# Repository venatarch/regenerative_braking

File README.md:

# Regenerative Braking Energy Recovery Circuit

## Objective

Recover braking energy from a BLDC motor using bidirectional MOSFET switching.

## Hardware

- STM32
- MOSFET Driver
- Current Sensor
- Voltage Sensor

## Software

- KiCad
- MATLAB
- STM32CubeIDE

## Status

- [x] Literature Review
- [ ] Schematic
- [ ] PCB
- [ ] Firmware
- [ ] Testing

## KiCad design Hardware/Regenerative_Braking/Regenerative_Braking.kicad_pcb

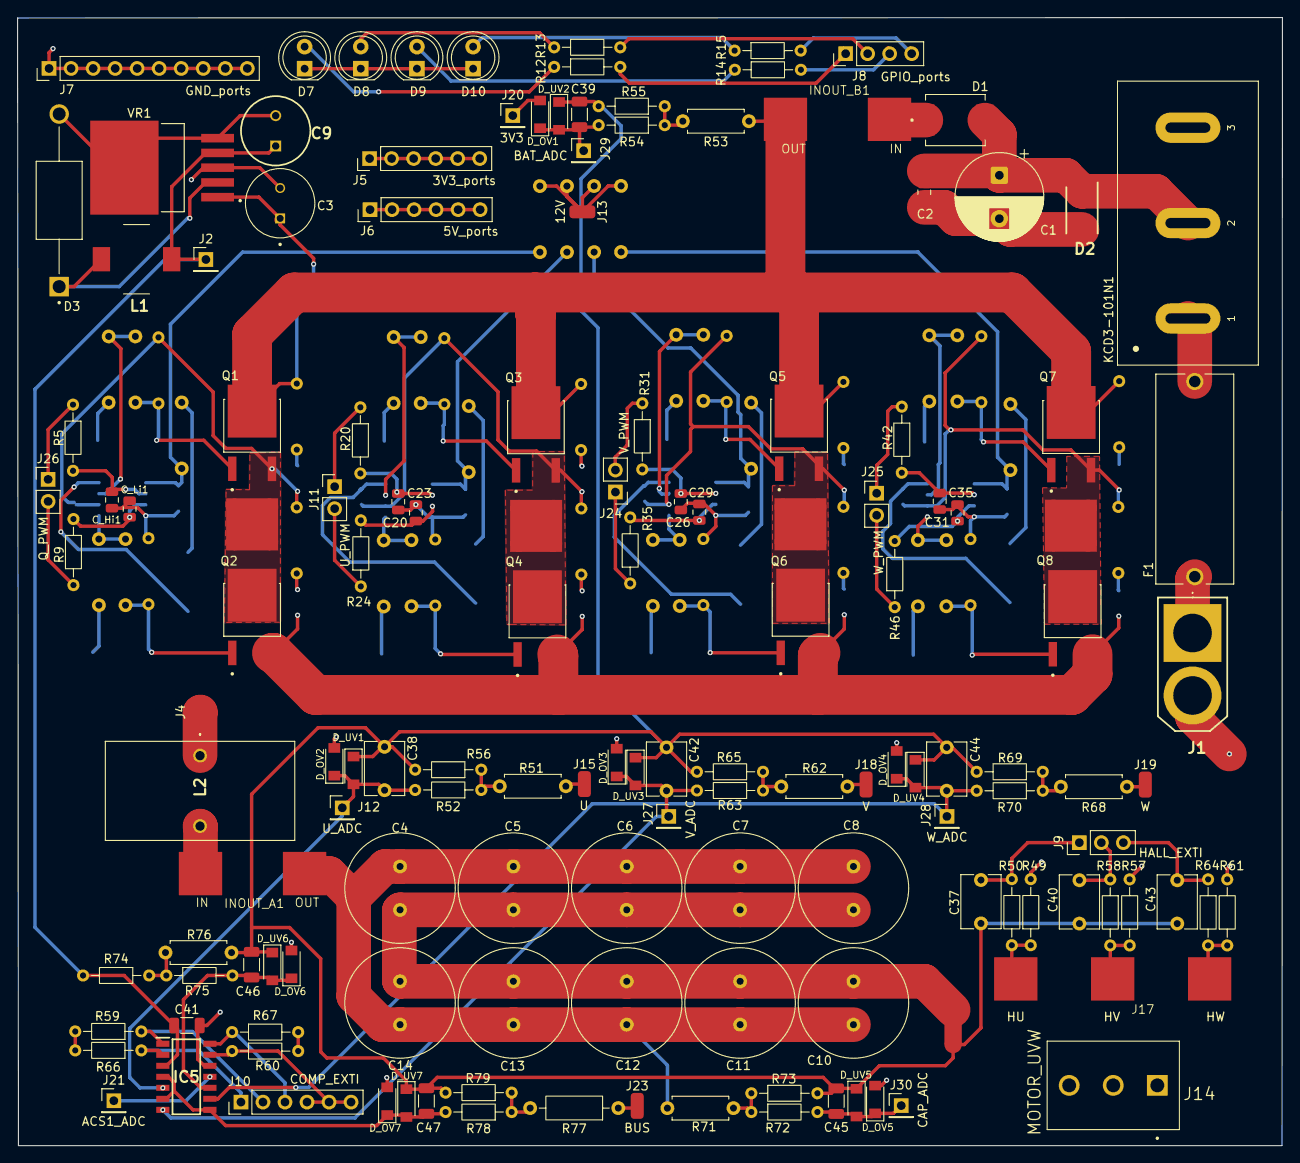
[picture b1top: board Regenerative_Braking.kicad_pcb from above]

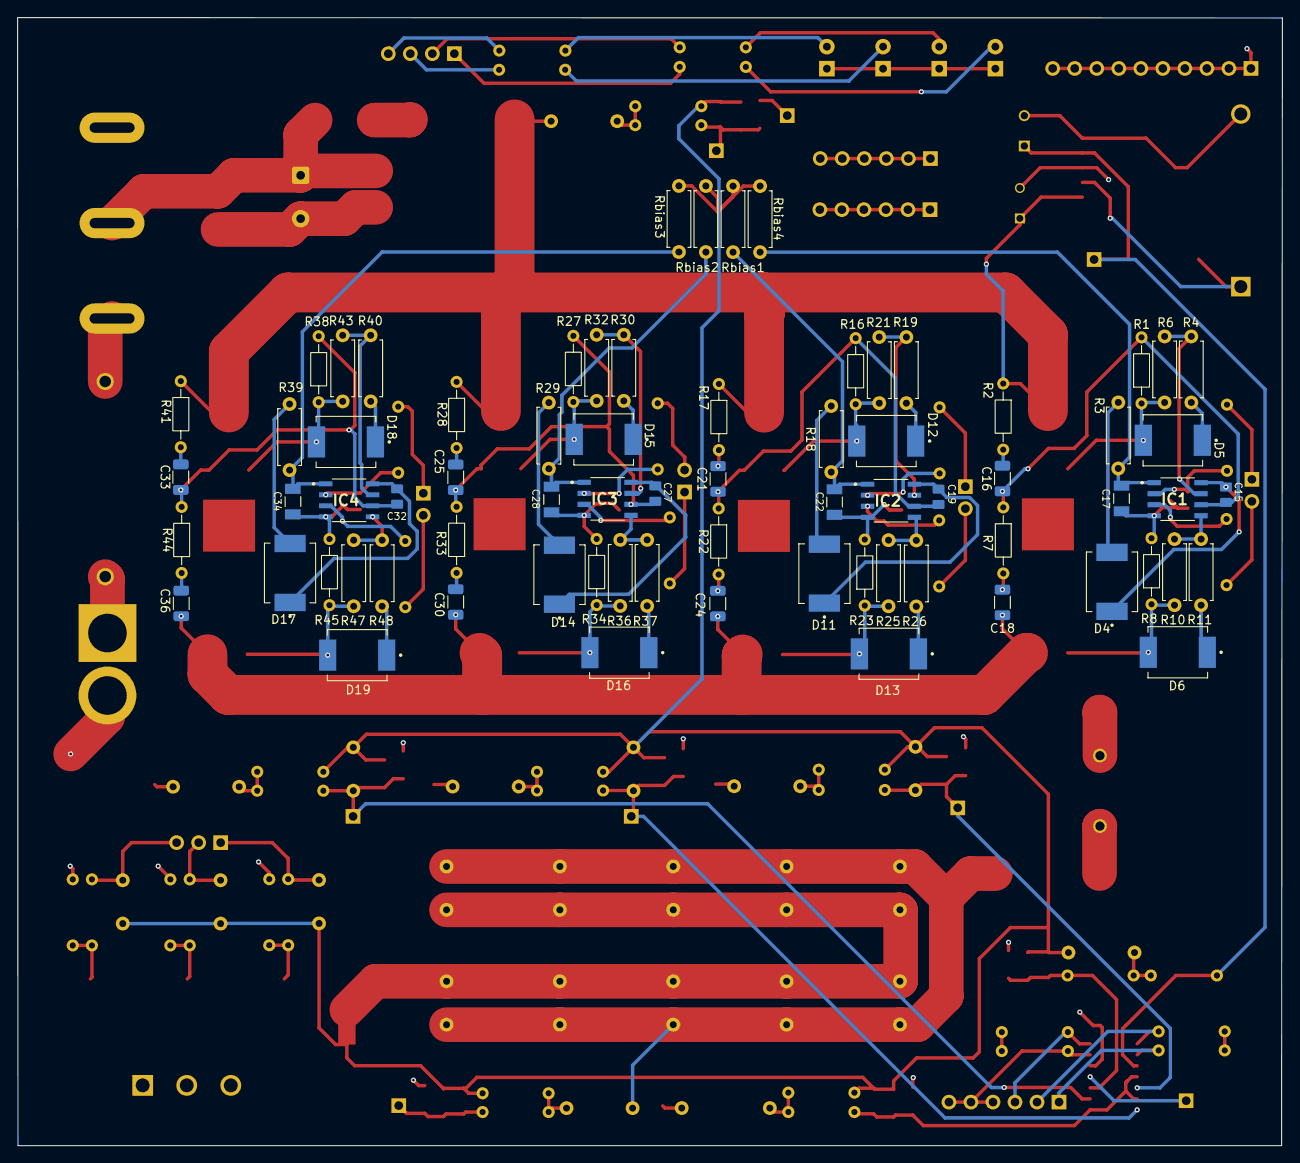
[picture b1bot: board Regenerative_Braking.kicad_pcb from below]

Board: 4 copper layers, 145.8 x 130.1 mm, 217 parts (72 on the bottom side), 115 nets.

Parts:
C1: 330u; CP_Radial_D10.0mm_P5.00mm
C2: 1u; C_0805_2012Metric
C3: 120uf; 120uf_cap_5v_buck
C4, C5, C6, C7, C8, C10, C11, C12, C13, C14: 1000uf; C_Radial_D12.5mm_H25.0mm_P5.00mm
C9: 330uf; 330uf_25v_cap_5v_buck
C15, C19, C27, C32: 0.47uf_50v_BScap
C16, C18, C21, C24, C25, C30, C33, C36: 1nf_snubber; C_1206_3216Metric
C17, C22, C28, C34: 4.7uf_50v_VDDcap
C20, C23, C26, C29, C31, C35: 33p; C_0805_2012Metric
C37, C38, C40, C42, C43, C44: 10nf_rcFilter; C_Disc_D6.0mm_W4.4mm_P5.00mm
C39, C41, C45, C46, C47: 100nf_rcFilter; C_1206_3216Metric
C_Hi1: 33p; C_0805_2012Metric
C_Li1: 33p; C_0805_2012Metric
D1: SS34; DIO_SS34
D2: SMBJ33A; DIOM5336X244N
D3: 1N5822; DIOAD1990W125L900D530
D4, D11, D14, D17: D_boot; boot_diode
D5: SS34_H; DIO_SS34
D6: SS34_L; DIO_SS34
D7, D8, D9, D10: LED; LED_D5.0mm
D12: SS34_UH; DIO_SS34
D13: SS34_UL; DIO_SS34
D15: SS34_VH; DIO_SS34
D16: SS34_VL; DIO_SS34
D18: SS34_WH; DIO_SS34
D19: SS34_WL; DIO_SS34
D_OV1, D_OV2, D_OV3, D_OV4, D_OV5, D_OV6, D_OV7: BAT54T1G; SODFL3718X115
D_UV1, D_UV2, D_UV3, D_UV4, D_UV5, D_UV6, D_UV7: BAT54T1G; SODFL3718X115
F1: 4628; FUSE_4628
IC1, IC2, IC3, IC4: UCC27710DR
IC5: LM339DT; SOIC127P600X175-14N
INOUT_A1: ACS_pad
INOUT_B1: ACS_pad
J1: XT60PB-M; XT60PBM
J2: 5V; PinHeader_1x01_P2.54mm_Vertical
J4: L_in; SolderWirePad_1x01_SMD_1.5x3mm
J5: 3V3_ports; PinHeader_1x06_P2.54mm_Vertical
J6: 5V_ports; PinHeader_1x06_P2.54mm_Vertical
J7: GND_ports; PinHeader_1x10_P2.54mm_Vertical
J8: GPIO_ports; PinHeader_1x04_P2.54mm_Vertical
J9: HALL_EXTI; PinHeader_1x03_P2.54mm_Vertical
J10: COMP_EXTI; PinHeader_1x06_P2.54mm_Vertical
J11: U_PWM; PinHeader_1x02_P2.54mm_Vertical
J12: U_ADC; PinHeader_1x01_P2.54mm_Vertical
J13: 12V; SolderWirePad_1x01_SMD_1.5x3mm
J14: MOTOR_UVW; CUI_TB004-508-03BE
J15: U; SolderWirePad_1x01_SMD_1.5x3mm
J17: HALL_EXTI; Hall_UVW
J18: V; SolderWirePad_1x01_SMD_1.5x3mm
J19: W; SolderWirePad_1x01_SMD_1.5x3mm
J20: 3V3; PinHeader_1x01_P2.54mm_Vertical
J21: ACS1_ADC; PinHeader_1x01_P2.54mm_Vertical
J23: BUS; SolderWirePad_1x01_SMD_1.5x3mm
J24: V_PWM; PinHeader_1x02_P2.54mm_Vertical
J25: W_PWM; PinHeader_1x02_P2.54mm_Vertical
J26: Q_PWM; PinHeader_1x02_P2.54mm_Vertical
J27: V_ADC; PinHeader_1x01_P2.54mm_Vertical
J28: W_ADC; PinHeader_1x01_P2.54mm_Vertical
J29: BAT_ADC; PinHeader_1x01_P2.54mm_Vertical
J30: CAP_ADC; PinHeader_1x01_P2.54mm_Vertical
KCD3-101N1: Switch_Rocker_KCD3-101N
L1: 47uH; CDRH8D43NP220NC
L2: 33uh; L_bdc
NT1: NetTie_2; NetTie-2_SMD_Pad2.0mm
NT2, NT3, NT4, NT5: NetTie_4_Cross; NetTie-4_SMD_Pad2.0mm
Q1, Q2, Q3, Q4, Q5, Q6, Q7, Q8: IRLR3705ZPBF
R1, R8, R16, R23, R27, R34, R38, R45, R49, R55, R56, R57, R59, R60, R61, R65, R66, R67, R69, R73, R79: 10k; R_Axial_DIN0204_L3.6mm_D1.6mm_P7.62mm_Horizontal
R2, R7, R17, R22, R28, R33, R41, R44: 22ohm_snubber; R_Axial_DIN0204_L3.6mm_D1.6mm_P7.62mm_Horizontal
R3, R18, R29, R39: 2.2; R_Axial_DIN0207_L6.3mm_D2.5mm_P7.62mm_Horizontal
R4, R11, R19, R26, R30, R37, R40, R48: 4.7; R_Axial_DIN0207_L6.3mm_D2.5mm_P7.62mm_Horizontal
R5, R9, R20, R24, R31, R35, R42, R46: 47; R_Axial_DIN0204_L3.6mm_D1.6mm_P7.62mm_Horizontal
R6, R10, R21, R25, R32, R36, R43, R47: 10; R_Axial_DIN0207_L6.3mm_D2.5mm_P7.62mm_Horizontal
R12, R13, R14, R15: 22; R_Axial_DIN0204_L3.6mm_D1.6mm_P7.62mm_Horizontal
R50, R52, R58, R63, R64, R70, R74: 1k; R_Axial_DIN0204_L3.6mm_D1.6mm_P7.62mm_Horizontal
R51, R53, R62, R68, R71: 100k; R_Axial_DIN0207_L6.3mm_D2.5mm_P7.62mm_Horizontal
R54, R72, R75, R78: 4.7k; R_Axial_DIN0204_L3.6mm_D1.6mm_P7.62mm_Horizontal
R76: 2.2k; R_Axial_DIN0207_L6.3mm_D2.5mm_P7.62mm_Horizontal
R77: 220K; R_Axial_DIN0207_L6.3mm_D2.5mm_P10.16mm_Horizontal
Rbias1, Rbias2, Rbias3, Rbias4: 10; R_Axial_DIN0207_L6.3mm_D2.5mm_P7.62mm_Horizontal
VR1: LM2596S-5.0; 5v_buck

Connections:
3V3: D_OV1.2, D_OV2.2, D_OV3.2, D_OV4.2, D_OV5.2, D_OV6.2, D_OV7.2, J20.1 (Pin_1_1), R49.2, R57.2, R59.2, R60.2, R61.2, R66.2, R67.2
5V: C9.1 (+), C41.1, IC5.3 (VCC+), J2.1 (Pin_1_1), L1.2, R74.1, VR1.4 (FEEDBACK)
12V: J13.1 (Pin_1_1), Rbias1.1, Rbias2.1, Rbias3.1, Rbias4.1
/Battery & Super Capacitor Buffer/GH: D5.A, Q1.1 (G), R1.1, R6.2
/Battery & Super Capacitor Buffer/GL: D6.A, Q2.1 (G), R8.1, R10.2
/Battery & Super Capacitor Buffer/HIN: C_Hi1.1, IC1.2 (HI), R5.2
/Battery & Super Capacitor Buffer/LIN: C_Li1.1, IC1.3 (LI), R9.2
/Battery & Super Capacitor Buffer/QH_out: IC1.7 (HO), R4.1, R6.1
/Battery & Super Capacitor Buffer/QL_out: IC1.5 (LO), R10.1, R11.1
/Battery & Super Capacitor Buffer/SW: D3.C, L1.1, VR1.2 (OUTPUT)
/Battery & Super Capacitor Buffer/VB: C15.1, D4.1 (K), IC1.8 (HB)
/Battery & Super Capacitor Buffer/VS: C15.2, C16.2, IC1.6 (HS), NT2.1, NT2.2, NT2.3, NT2.4, Q1.3 (S), Q2.2 (D), R1.2, R7.1
/Inverter Stage/GH1: D12.A, Q3.1 (G), R16.1, R21.2
/Inverter Stage/GH2: D15.A, Q5.1 (G), R27.1, R32.2
/Inverter Stage/GH3: D18.A, Q7.1 (G), R38.1, R43.2
/Inverter Stage/GL1: D13.A, Q4.1 (G), R23.1, R25.2
/Inverter Stage/GL2: D16.A, Q6.1 (G), R34.1, R36.2
/Inverter Stage/GL3: D19.A, Q8.1 (G), R45.1, R47.2
/Inverter Stage/U_HIN: C20.1, IC2.2 (HI), R20.2
/Inverter Stage/U_HOUT: IC2.7 (HO), R19.1, R21.1
/Inverter Stage/U_LIN: C23.1, IC2.3 (LI), R24.2
/Inverter Stage/U_LOUT: IC2.5 (LO), R25.1, R26.1
/Inverter Stage/VB_1: C19.1, D11.1 (K), IC2.8 (HB)
/Inverter Stage/VB_2: C27.1, D14.1 (K), IC3.8 (HB)
/Inverter Stage/VB_3: C32.1, D17.1 (K), IC4.8 (HB)
/Inverter Stage/VS_1: C19.2, C21.2, IC2.6 (HS), NT3.1, NT3.2, NT3.3, NT3.4, Q3.3 (S), Q4.2 (D), R16.2, R22.1
/Inverter Stage/VS_2: C25.2, C27.2, IC3.6 (HS), NT4.1, NT4.2, NT4.3, NT4.4, Q5.3 (S), Q6.2 (D), R27.2, R33.1
/Inverter Stage/VS_3: C32.2, C33.2, IC4.6 (HS), NT5.1, NT5.2, NT5.3, NT5.4, Q7.3 (S), Q8.2 (D), R38.2, R44.1
/Inverter Stage/V_HIN: C26.1, IC3.2 (HI), R31.2
/Inverter Stage/V_HOUT: IC3.7 (HO), R30.1, R32.1
/Inverter Stage/V_LIN: C29.1, IC3.3 (LI), R35.2
/Inverter Stage/V_LOUT: IC3.5 (LO), R36.1, R37.1
/Inverter Stage/W_HIN: C31.1, IC4.2 (HI), R42.2
/Inverter Stage/W_HOUT: IC4.7 (HO), R40.1, R43.1
/Inverter Stage/W_LIN: C35.1, IC4.3 (LI), R46.2
/Inverter Stage/W_LOUT: IC4.5 (LO), R47.1, R48.1
/Sensors/HU: J17.1, R49.1, R50.2
/Sensors/HV: J17.2, R57.1, R58.2
/Sensors/HW: J17.3, R61.1, R64.2
ACS1: IC5.11 (NON-INVERTING_INPUT4), J21.1 (Pin_1_1)
ACS_in: INOUT_A1.1 (IN), L2.2
Cap_bufferBank: C4.1, C5.1, C6.1, C7.1, C8.1, C10.1, C11.1, C12.1, C13.1, C14.1, INOUT_A1.2 (OUT), R71.1
DC_BUS: D1.C, INOUT_B1.1 (IN)
GND: C1.2, C2.2, C3.N, C4.2, C5.2, C6.2, C7.2, C8.2, C9.2 (-), C10.2, C11.2, C12.2, C13.2, C14.2, C17.2, C18.2, C20.2, C22.2, C23.2, C24.2, C26.2, C28.2, C29.2, C30.2, C31.2, C34.2, C35.2, C36.2, C41.2, C_Hi1.2, C_Li1.2, D2.2 (A), D3.A, D7.1 (K), D8.1 (K), D9.1 (K), D10.1 (K), IC1.4 (COM), IC2.4 (COM), IC3.4 (COM), IC4.4 (COM), IC5.12 (VCC-), J1.2 (-), J7.1, J7.2, J7.3, J7.4, J7.5, J7.6, J7.7, J7.8, J7.9, J7.10, NT1.2, Q2.3 (S), Q4.3 (S), Q6.3 (S), Q8.3 (S), R8.2, R23.2, R34.2, R45.2, VR1.3 (GROUND), VR1.5 (~ON/OFF), VR1.6 (GND_TAB)
GNDA: C37.2, C38.2, C39.2, C40.2, C42.2, C43.2, C44.2, C45.2, C46.2, C47.2, D_UV1.1, D_UV2.1, D_UV3.1, D_UV4.1, D_UV5.1, D_UV6.1, D_UV7.1, NT1.1, R55.2, R56.2, R65.2, R69.2, R73.2, R76.1, R79.2
Hall_U: C37.1, J9.1, R50.1
Hall_V: C40.1, J9.2, R58.1
Hall_W: C43.1, J9.3, R64.1
unnamed: C16.1, R2.2
unnamed: C18.1, R7.2
unnamed: C21.1, R17.2
unnamed: C24.1, R22.2
unnamed: C25.1, R28.2
unnamed: C30.1, R33.2
unnamed: C33.1, R41.2
unnamed: C36.1, R44.2
unnamed: C1.1, C2.1, D1.A, D2.1 (K), KCD3-101N1.2 (Load)
unnamed: D4.2 (A), R3.2
unnamed: D5.C, R4.2
unnamed: D6.C, R11.2
unnamed: D7.2 (A), R12.1
unnamed: D8.2 (A), R13.1
unnamed: D9.2 (A), R14.1
unnamed: D10.2 (A), R15.1
unnamed: D11.2 (A), R18.2
unnamed: D12.C, R19.2
unnamed: D13.C, R26.2
unnamed: D14.2 (A), R29.2
unnamed: D15.C, R30.2
unnamed: D16.C, R37.2
unnamed: D17.2 (A), R39.2
unnamed: D18.C, R40.2
unnamed: D19.C, R48.2
unnamed: F1.1, J1.1 (+)
unnamed: J4.1 (Pin_1_1), L2.1
unnamed: J8.1, R12.2
unnamed: J8.2, R13.2
unnamed: J8.3, R14.2
unnamed: J8.4, R15.2
unnamed: J15.1 (Pin_1_1), R51.1
unnamed: J18.1 (Pin_1_1), R62.1
unnamed: J19.1 (Pin_1_1), R68.1
unnamed: J23.1 (Pin_1_1), R77.1
unnamed: F1.2, KCD3-101N1.1 (Line)
unnamed: R51.2, R52.1, R56.1
unnamed: R53.2, R54.1, R55.1
unnamed: R62.2, R63.1, R65.1
unnamed: R68.2, R69.1, R70.1
unnamed: R71.2, R72.1, R73.1
unnamed: R74.2, R75.1, R76.2
unnamed: R77.2, R78.1, R79.1
OC_mid: C46.1, D_OV6.1, D_UV6.2, IC5.10 (INVERTING_INPUT4), R75.2
OUT1: IC5.2 (OUTPUT1), J10.1, R66.1
OUT2: IC5.1 (OUTPUT2), J10.2, R59.1
OUT3: IC5.14 (OUTPUT3), J10.3, R67.1
OUT4: IC5.13 (OUTPUT4), J10.4, J10.5, J10.6, R60.1
Q_HIGH: J26.1, R5.1
Q_LOW: J26.2, R9.1
REF: C47.1, D_OV7.1, D_UV7.2, IC5.4 (INVERTING_INPUT1), IC5.6 (INVERTING_INPUT2), IC5.8 (INVERTING_INPUT3), R78.2
U_ADC1: C38.1, D_OV2.1, D_UV1.2, IC5.5 (NON-INVERTING_INPUT_1), J12.1 (Pin_1_1), R52.2
U_HIGH: J11.1, R20.1
U_LOW: J11.2, R24.1
VBUS: C3.P, INOUT_B1.2 (OUT), Q1.2 (D), Q3.2 (D), Q5.2 (D), Q7.2 (D), R2.1, R17.1, R28.1, R41.1, R53.1, VR1.1 (VIN)
VDD: C17.1, IC1.1 (VDD), R3.1, Rbias4.2
VSENSE_BAT: C39.1, D_OV1.1, D_UV2.2, J29.1 (Pin_1_1), R54.2
VSENSE_CAP: C45.1, D_OV5.1, D_UV5.2, J30.1 (Pin_1_1), R72.2
V_ADC1: C42.1, D_OV3.1, D_UV3.2, IC5.7 (NON-INVERTING_INPUT2), J27.1 (Pin_1_1), R63.2
V_HIGH: J24.2, R31.1
V_LOW: J24.1, R35.1
Vcc_12v_1: C22.1, IC2.1 (VDD), R18.1, Rbias1.2
Vcc_12v_2: C28.1, IC3.1 (VDD), R29.1, Rbias2.2
Vcc_12v_3: C34.1, IC4.1 (VDD), R39.1, Rbias3.2
W_ADC1: C44.1, D_OV4.1, D_UV4.2, IC5.9 (NON-INVERTING_INPUT3), J28.1 (Pin_1_1), R70.2
W_HIGH: J25.1, R42.1
W_LOW: J25.2, R46.1
